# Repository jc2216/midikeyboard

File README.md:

# midikeyboard

## Intro
- This project was built for HackClub HalfLife because I really want a 3D printer.
- This is a MIDI Keyboard that will play notes when you press on the capacitive keys and the switches. Cool lights will also happen through the LEDs. The function of the rotary encoder is currently to be determined until I write the complete firmware. I decided to not use the potentiometer because I didn't really want to source anything outside of Aliexpress.

## Features
- Waveshare Esp-32 S3 Zero
- LED
- Kailh Choc Low-Profile Switches
- Rotary Encoder

## Schematic

- There are 3 switches, 8 capacitive touch keys, 1 rotary encoder, 3 LEDs, and 1 esp-32. The capacitive touch buttons are wired to pins on the esp-32.

## PCB

- I drew some funny pictures on the front and the back.
- It's basically the schematic but in 3D.
- Creating footprints for the capacitive touch keys took a long time, but basically, you have to keep merging the graphic elements with the pads for each individual pad.
- Routing kind of sucked, too, because the blue lines kept crossing each other. Had to change the schematic to get it to work.

## Enclosure

https://cad.onshape.com/documents/4fc3b71b01772681d883c97f/w/cad2a5591ffdc3dc252a0036/e/84e5be4e2e1320dfb467a09a

- I cadded up an enclosure for the PCB so that it's easier to hold and there's more protection.
- I'm not sure if this is the right way to CAD the enclosure but it looks okay for now.
- There are holes for M3 screws to fasten the two components.
- Need to check: the PCB may wobble in the enclosure. May need to tighten up clearance.

## Firmware
- Currently, very in progress.
- I got really confused with the firmware and CircuitPython and KMK.
- I decided to just get the template code from the guide, and then change the pin numbers to reflect my schematic.
- Will be working on firmware during build week.
- I also don't really know how to upload the firmware to the microcontroller, so will also figure that out during build week (it's probably easier when I have the physical board anyway).

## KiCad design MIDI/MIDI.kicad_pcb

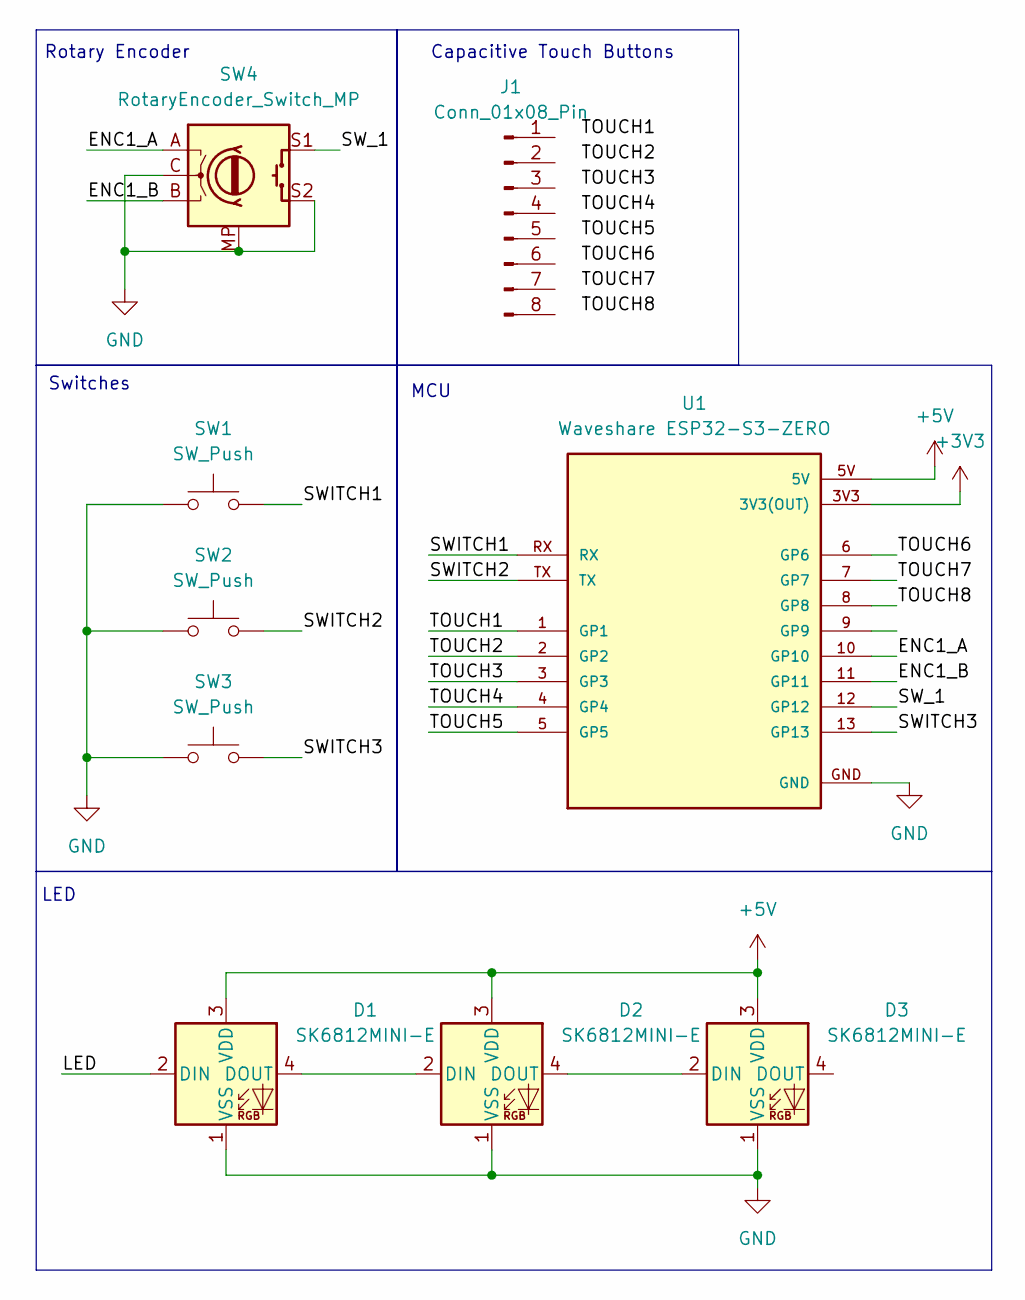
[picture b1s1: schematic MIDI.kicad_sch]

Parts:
D1, D2, D3: SK6812MINI-E; LED_SK6812MINI-E_3.2x2.8mm_P1.5mm_ReverseMount
J1: Conn_01x08_Pin; capacitive keys
SW1, SW2, SW3: SW_Push; Kailh Choc Low-Profile Switches
SW4: RotaryEncoder_Switch_MP; RotaryEncoder_Alps_EC11E-Switch_Vertical_H20mm
U1: Waveshare ESP32-S3-ZERO; Waveshare ESP32-S3-Zero; PARTREV NA

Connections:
+3V3: U1.3V3 (3V3(OUT))
+5V: D1.3 (VDD), D2.3 (VDD), D3.3 (VDD), U1.5V
/ENC1_A: SW4.A, U1.10 (GP10)
/ENC1_B: SW4.B, U1.11 (GP11)
/LED: D1.2 (DIN)
/SWITCH1: SW1.2, U1.RX
/SWITCH2: SW2.2, U1.TX
/SWITCH3: SW3.2, U1.13 (GP13)
/SW_1: SW4.S1, U1.12 (GP12)
/TOUCH1: U1.1 (GP1)
/TOUCH2: U1.2 (GP2)
/TOUCH3: U1.3 (GP3)
/TOUCH4: U1.4 (GP4)
/TOUCH5: U1.5 (GP5)
/TOUCH6: U1.6 (GP6)
/TOUCH7: U1.7 (GP7)
/TOUCH8: U1.8 (GP8)
GND: D1.1 (VSS), D2.1 (VSS), D3.1 (VSS), SW1.1, SW2.1, SW3.1, SW4.C, SW4.MP, SW4.S2, U1.GND
unnamed: D1.4 (DOUT), D2.2 (DIN)
unnamed: D2.4 (DOUT), D3.2 (DIN)

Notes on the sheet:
Capacitive Touch Buttons
MCU
LED
Rotary Encoder
Switches

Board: 2 copper layers, 9 parts (3 on the bottom side), 10 nets, no tracks yet.

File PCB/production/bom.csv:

Designator,Footprint,Quantity,Value,LCSC Part #
"D1, D2, D3",LED_SK6812MINI-E_3.2x2.8mm_P1.5mm_ReverseMount,3,SK6812MINI-E,
J1,new keys!,1,Conn_01x08_Pin,
"SW1, SW2, SW3",Kailh Choc Low-Profile Switches,3,SW_Push,
SW4,RotaryEncoder_Alps_EC11E-Switch_Vertical_H20mm,1,RotaryEncoder_Switch_MP,
U1,Waveshare ESP32-S3-Zero,1,Waveshare ESP32-S3-ZERO,
